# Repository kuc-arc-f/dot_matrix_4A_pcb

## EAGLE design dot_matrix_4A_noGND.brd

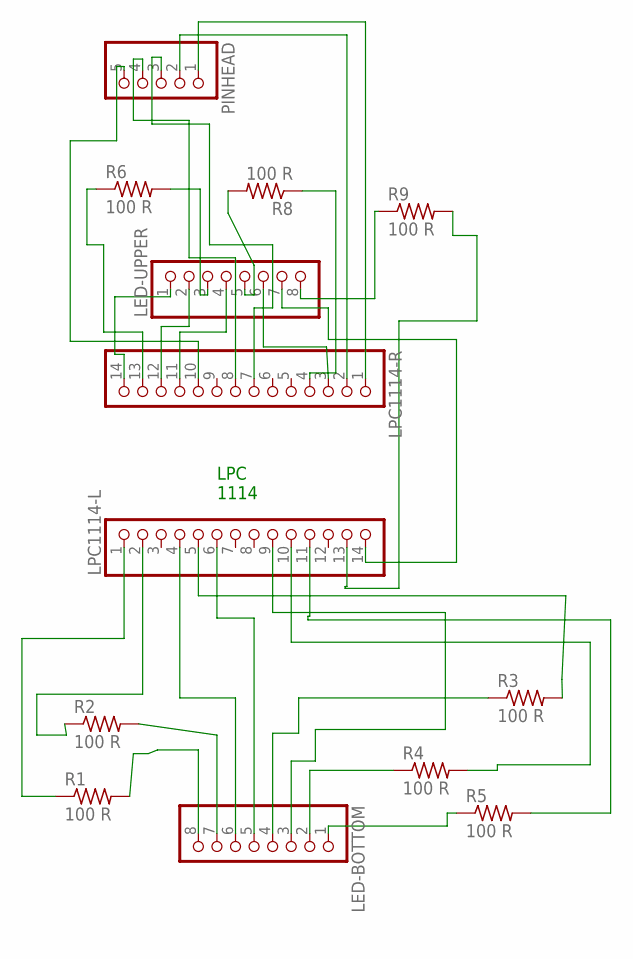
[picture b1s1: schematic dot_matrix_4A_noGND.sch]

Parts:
LED-BOTTOM: PINHD-1X8; 1X08
LED-UPPER: PINHD-1X8; 1X08
LPC1114-L, LPC1114-R: PINHD-1X14; 1X14
PINHEAD: PINHD-1X5; 1X05
R1, R2, R3, R4, R5, R6, R8, R9: 100 R; 0204/7

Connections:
unnamed: LED-UPPER.8, R9.1
unnamed: LPC1114-L.1, R1.1
unnamed: LPC1114-L.2, R2.1
unnamed: LED-UPPER.1, LPC1114-R.14
unnamed: LED-BOTTOM.8, R1.2
unnamed: LED-BOTTOM.7, R2.2
unnamed: LPC1114-L.11, R5.2
unnamed: LED-BOTTOM.6, LPC1114-L.4
unnamed: LED-BOTTOM.5, LPC1114-L.6
unnamed: LPC1114-R.10, PINHEAD.5
unnamed: LPC1114-R.8, PINHEAD.4
unnamed: LPC1114-R.7, PINHEAD.3
unnamed: LPC1114-R.2, PINHEAD.2
unnamed: LED-BOTTOM.2, R4.1
unnamed: LPC1114-L.10, R4.2
unnamed: LED-BOTTOM.1, R5.1
unnamed: LPC1114-R.1, PINHEAD.1
unnamed: LED-BOTTOM.4, R3.1
unnamed: LPC1114-L.5, R3.2
unnamed: LED-BOTTOM.3, LPC1114-L.9
unnamed: LED-UPPER.2, LPC1114-R.12
unnamed: LPC1114-R.13, R6.1
unnamed: LED-UPPER.4, LPC1114-R.11
unnamed: LED-UPPER.5, R8.2
unnamed: LPC1114-R.4, R8.1
unnamed: LED-UPPER.3, R6.2
unnamed: LED-UPPER.6, LPC1114-R.3
unnamed: LED-UPPER.7, LPC1114-L.14
unnamed: LPC1114-L.13, R9.2

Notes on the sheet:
LPC 1114

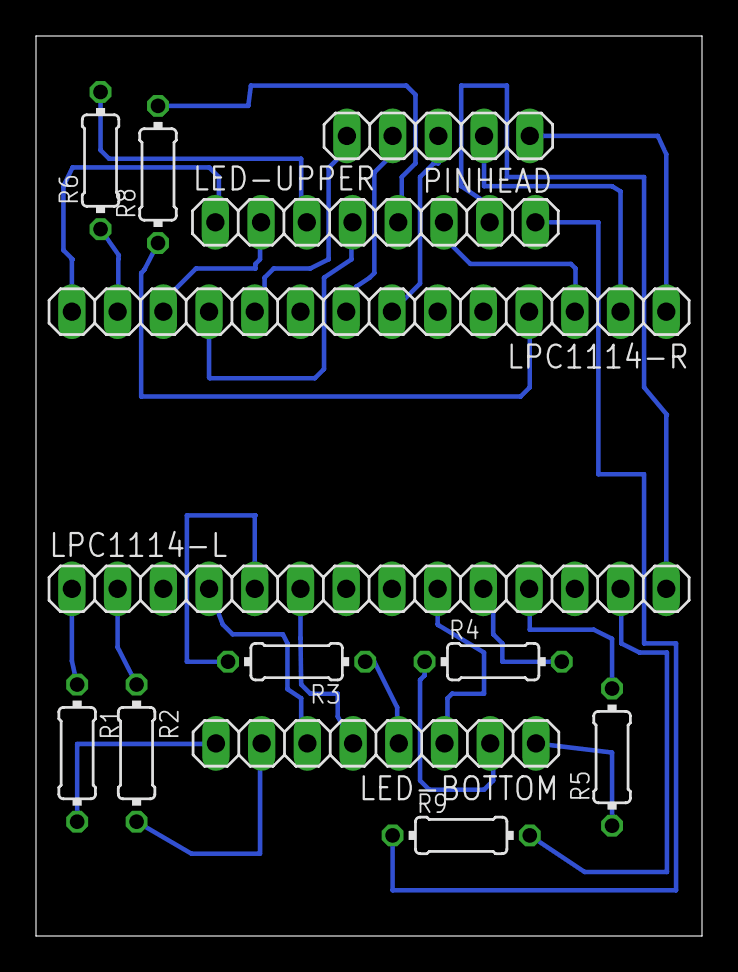
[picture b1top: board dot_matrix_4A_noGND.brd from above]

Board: 2 copper layers, 37.0 x 50.0 mm, 13 parts (0 on the bottom side), 29 nets.

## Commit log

2017-08-17 new ,08-17a1
